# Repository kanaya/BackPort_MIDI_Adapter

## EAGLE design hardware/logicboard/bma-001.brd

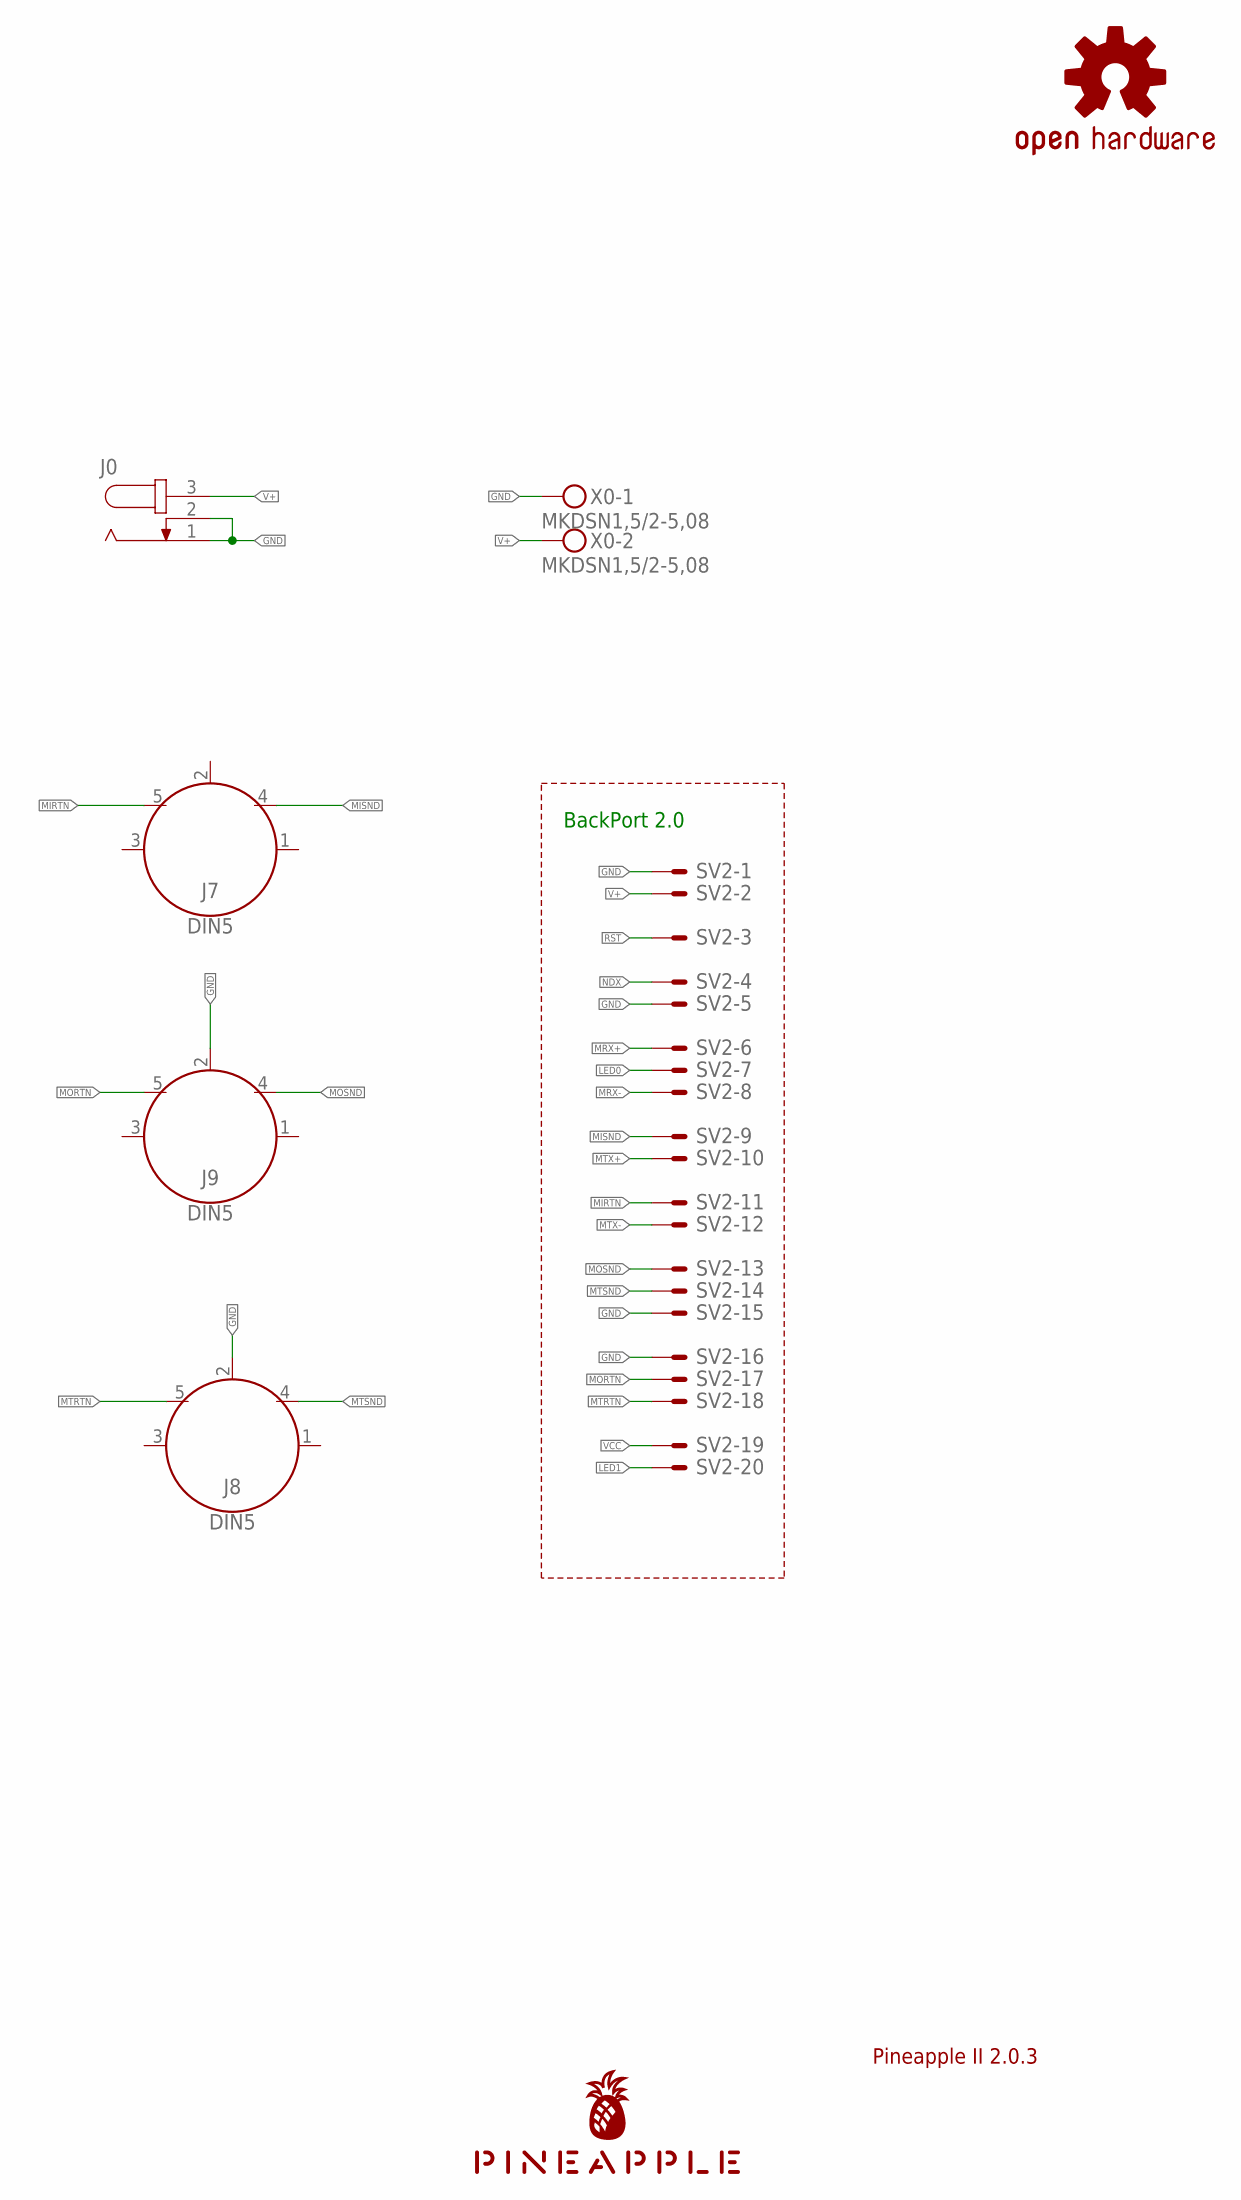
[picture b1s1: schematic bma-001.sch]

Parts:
J0: JACK-PLUG0; SPC4077
J7, J8, J9: DIN5; DIN5-RA-PTH
LOGO1: OSHW-LOGOS-COPPER; OSHW-LOGO-S_COPPER
SV2: ML20LE; ML20L
U$1: PINEAPPLE450_SILK
X0: MKDSN1,5/2-5,08

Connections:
GND: J0.1, J0.2, J8.2, J9.2, SV2.1, SV2.5, SV2.15, SV2.16, X0.1
LED0: SV2.7
LED1: SV2.20
MIRTN: J7.5, SV2.11
MISND: J7.4, SV2.9
MORTN: J9.5, SV2.17
MOSND: J9.4, SV2.13
MRX+: SV2.6
MRX-: SV2.8
MTRTN: J8.5, SV2.18
MTSND: J8.4, SV2.14
MTX+: SV2.10
MTX-: SV2.12
NDX: SV2.4
RST: SV2.3
V+: J0.3, SV2.2, X0.2
VCC: SV2.19

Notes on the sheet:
Pineapple II 2.0.3
BackPort 2.0

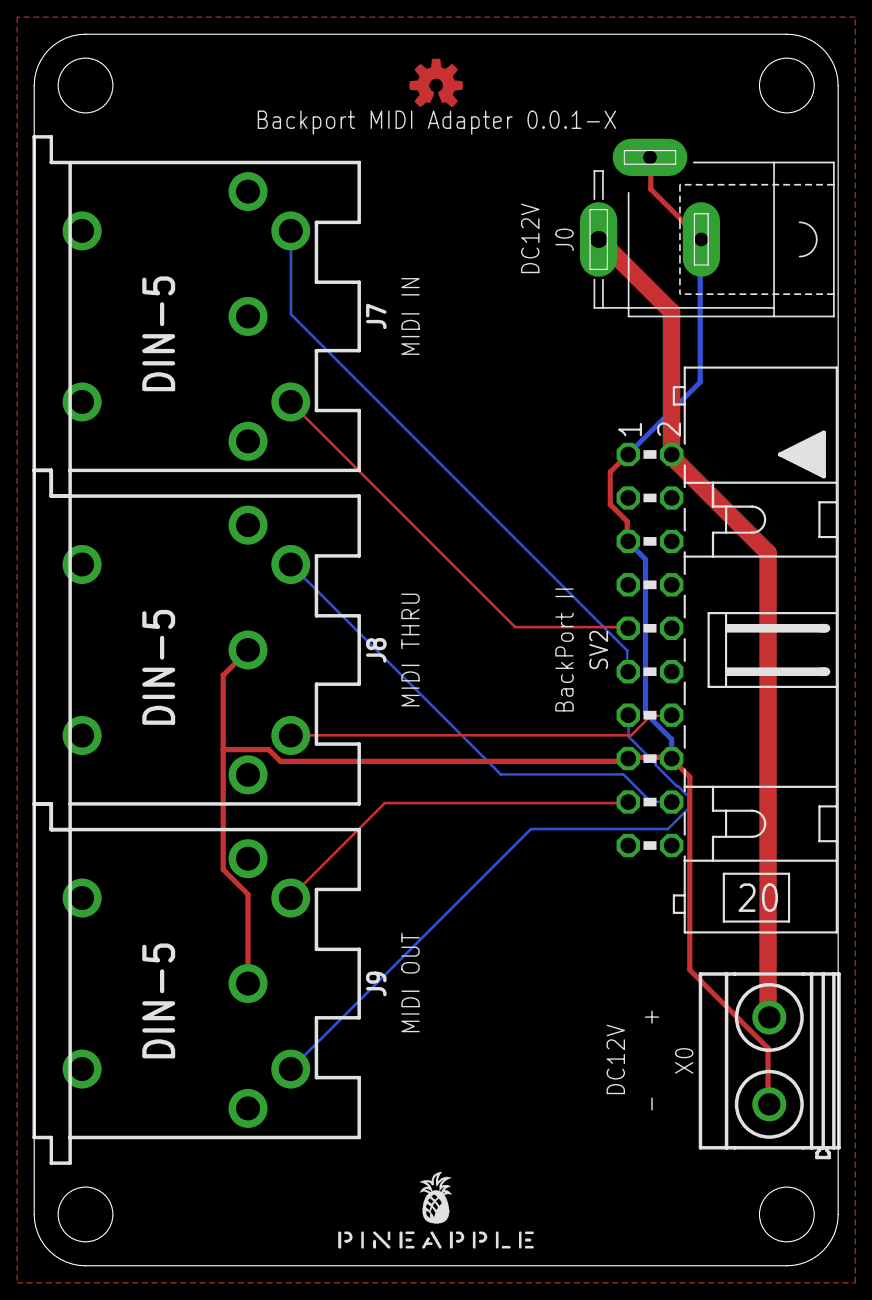
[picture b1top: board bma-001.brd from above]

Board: 2 copper layers, 47.0 x 72.0 mm, 8 parts (0 on the bottom side), 8 nets.

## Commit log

2022-09-18 Clean up.
2022-09-19 First working model.

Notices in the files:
parts and their libraries:
SparkFun-Aesthetics: Licensing: Creative Commons ShareAlike 4.0 International - https://creativecommons.org/licenses/by-sa/4.0
